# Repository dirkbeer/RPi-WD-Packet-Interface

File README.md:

Note: Schematic and board modified by dirkbeer to use an RJ-45 instead of a DB-9 connector. The RJ-45 pinout used is for the microphone connector on Baofeng mobile radios (e.g. UV-50x2). The text below is jaymzx's original readme.

# RPi-WD-Packet-Interface - A digital mode soundcard interface for the Raspberry Pi!

I set up an APRS igate using a Raspberry Pi device and a TNC-Pi 'hat'. While troubleshooting some other issues, I inadvertantly damaged the TNC-Pi, so I decided to go with a software TNC application. In this case, I chose [Dire Wolf](https://github.com/wb2osz/direwolf) by WB2OSZ. In his documentation, he specified a simple radio PTT interface that included a 'watchdog timer' to prevent a software issue from locking the radio into transmit. Working with WB2OSZ, I expanded the circuit and created a board with the following features:

### Selectable transmit and receive channels
* I noticed between sound card dongles, the mic input could be on the left or the right channel, depending on how much care the manufacturer put into it. A jumper lets you pick the channel that works with your card. I added a transmit channel selector for the same reason, but also so you can use a 'Y' cable with your stereo sound card and use two interfaces to work with two radios without any cable hacking.

### Transmit audio level pot
* The radio is expecting millivolts of input into its MIC input. Modern sound cards can put out more than 2V peak to peak. This is really bad for distortion and over-deviation. Right now, I use about 40% volume on the sound card, and 20% volume on the pot. The audio is DC isolated with a capacitor to prevent phantom voltage (for electret microphones) from either the sound card or the radio from damaging anything.

### Adjustable watchdog delay
* Most people will use this for packet, but some others may use it for things like RTTY, JT-65, QRSS or any other digital mode that has a long duty cycle. I added a big cap and 25-turn trimmer for a delay adjustable between 0 and 110 seconds with the parts specified. One can solder in a fixed resistor or change values for something that doesn't need to be adjusted. [Calculators](http://www.ohmslawcalculator.com/555-monostable-calculator) are out there.

### DCD (received packet) LED
* The newest version of Dire Wolf can trigger a GPIO pin to signal a successfully decoded packet. Just bring this pin 'high' and the yellow DCD LED will light up. Yay. Good for watching activity at-a-glance from across the shack.

### Selectable single-wire handheld PTT or 'Kenwood' dedicated PTT wire method
* Most HTs use a resistor to ground on the microphone input to trigger PTT. Kenwood/Baofeng and some others have to be different and ground the mic shield to trigger. You can set a jumper to select whatever method you need.
	
### Standard Kantronics DB-9 radio interface
* I already had some cables I made and bought for radios when using my KPC3. The TNC-Pi and (I believe) the TinyTrak and OpenTracker devices use the same standard. This makes it easy to buy cables if you don't want to make them, or re-use ones you already have kicking around. FWIW, I hate DB9 connectors and prefer RJ-45 for these purposes, but I wanted to make it 'standard'. Signalink and RigBlaster use a similar (although RB is reversed) RJ-45 standard, but it's not as prolific. In case someone hates DB-9 as much as I do, I called out the signals on the pads to which they can be directly soldered for a cable, header pins, etc.

### Native 3.3v Rpi logic levels
* Using this board as configured works with the 3.3v logic the RPi uses. If you use another controller (like an Arduino) you *can* use 5V logic as the LMC555 CMOS can handle it without a sweat, but you will need to change the resistor values for the LEDs and transistor bias. You can also skip 3.3v altogether if you want to use it with a 5V microcontroller and use a cheap and widely-available LM555N (and the appropriate resistor changes).

### Uses standard 60mm x 60mm 'Sick of Beige' PCB size
* Just like the [xkcd](https://xkcd.com/927/) comic about standards, there is a new PCB size standard for the Maker crowd called [Sick of Beige](http://dangerousprototypes.com/docs/Sick_of_Beige). They have some cool acrylic cases at [Seeed Studios](http://www.seeedstudio.com/depot/Sick-Of-Beige-Basic-Case-v1-60mm-Square-DP6060-p-1329.html), but you can probably find others or fab up your own. The original board was smaller, but in order to fit into the SoB standard size, the minimum size that would fit the DB-9 connector is 60mm. Please note this is *not* a 'hat' for the RPi. It's a separate board. 

### Open Hardware
* I put the time into it, but like most of my projects, once it's done, it's done. I figure others can benefit from my work, so I may as well pass it on. This project is licensed under [Creative Commons Attribution-ShareAlike](https://creativecommons.org/licenses/by-sa/3.0/), so you can edit it, improve it, remix it into another project, make and sell PCBs or kits, etc. You just need to specify a link back to the original source (here) to comply. It's no big deal.
		
### Readily-available parts
* You probably have most of these parts in your bin, but things like the 3.5mm and DB-9 connectors are available at [SparkFun](https://www.sparkfun.com/). I specified genuine Borne trimpots in the PCB footprints but they are commonly used by others. You can find them at [Mouser](http://www.mouser.com/) or many other places.

You can order a [pre-made PCB from OSH Park](https://oshpark.com/shared_projects/dotsia3r) (with the beautiful purple solder mask as shown). They come in multiples of three, so order some for your friends or make a couple for a multi-rig interface. You can also take the Eagle files and have them made elsewhere, or make your own using a toner transfer or photo etch PCB process. Go nuts.

# Known issues
None at this time. 

# Improvements
I'm kicking around the idea of an RJ-45 version of this board, which would be a simple redesign. I also have on the drawing board an isolated version with transformers and opto-isolated PTT control. I welcome discussion around this, and if you can't wait, feel free to fork this project!

## Enjoy the interface, and see you on the air.

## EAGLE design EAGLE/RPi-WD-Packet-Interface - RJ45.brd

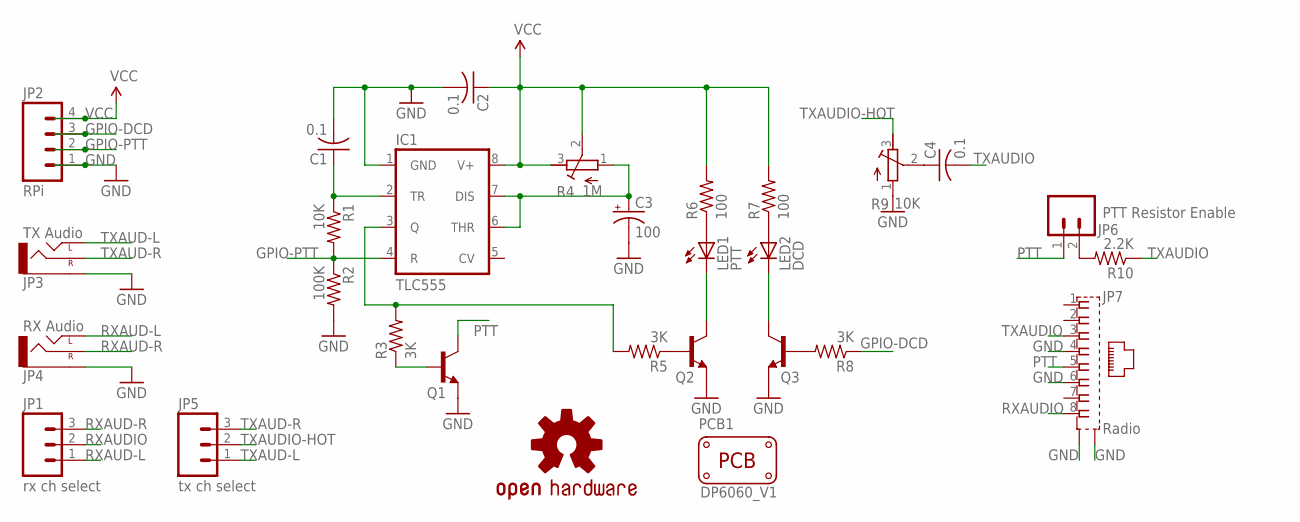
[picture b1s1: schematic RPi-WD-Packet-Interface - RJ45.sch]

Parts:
C1, C2, C4: 0.1; C025-025X050
C3: 100; E2-5
IC1: TLC555; DIL08
JP1: rx ch select; 1X03
JP2: RPi; 1X04
JP3: TX Audio; AUDIO-JACK
JP4: RX Audio; AUDIO-JACK
JP5: tx ch select; 1X03
JP6: PTT Resistor Enable; 1X02
JP7: Radio; 0446200002
LED1: PTT; LED5MM
LED2: DCD; LED5MM
LOGO1: OSHW-LOGOM; OSHW-LOGO-M
PCB1: PCB_DP_SQUARE-6X6; DP6060_V1
Q1: PTT; TO-92-AMMO
Q2: PTT-LED; TO-92-AMMO
Q3: DCD-LED; TO-92-AMMO
R1: 10K; 0207/7
R2: 100K; 0207/7
R3, R5, R8: 3K; 0207/7
R4: 1M; RTRIM3296W
R6, R7: 100; 0207/7
R9: 10K; RTRIM3362P
R10: 2.2K; 0207/7

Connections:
GND: C1.2, C2.2, C3.-, IC1.1 (GND), JP2.1, JP3.SLEEVE, JP4.SLEEVE, JP7.4, JP7.6, JP7.S@1 (S1), JP7.S@2 (S2), Q1.1 (E), Q2.1 (E), Q3.1 (E), R2.2, R9.1
GPIO-DCD: JP2.3, R8.1
GPIO-PTT: IC1.4 (R), JP2.2, R1.2, R2.1
unnamed: LED1.A, R6.1
unnamed: LED2.A, R7.1
unnamed: C1.1, IC1.2 (TR), R1.1
unnamed: C4.1, R9.2
unnamed: C3.+, IC1.6 (THR), IC1.7 (DIS), R4.1 (A)
unnamed: LED1.K (C), Q2.3 (C)
unnamed: Q2.2 (B), R5.1
unnamed: Q1.2 (B), R3.1
unnamed: LED2.K (C), Q3.3 (C)
unnamed: Q3.2 (B), R8.2
unnamed: JP6.2, R10.2
PTT: JP6.1, JP7.5, Q1.3 (C)
PTT_TRIGGER: IC1.3 (Q), R3.2, R5.2
RXAUD-L: JP1.1, JP4.TIP (LEFT)
RXAUD-R: JP1.3, JP4.RING (RIGHT)
RXAUDIO: JP1.2, JP7.8
TXAUD-L: JP3.TIP (LEFT), JP5.1
TXAUD-R: JP3.RING (RIGHT), JP5.3
TXAUDIO: C4.2, JP7.3, R10.1
TXAUDIO-HOT: JP5.2, R9.3
VCC: C2.1, IC1.8 (V+), JP2.4, R4.2 (S), R4.3 (E), R6.2, R7.2

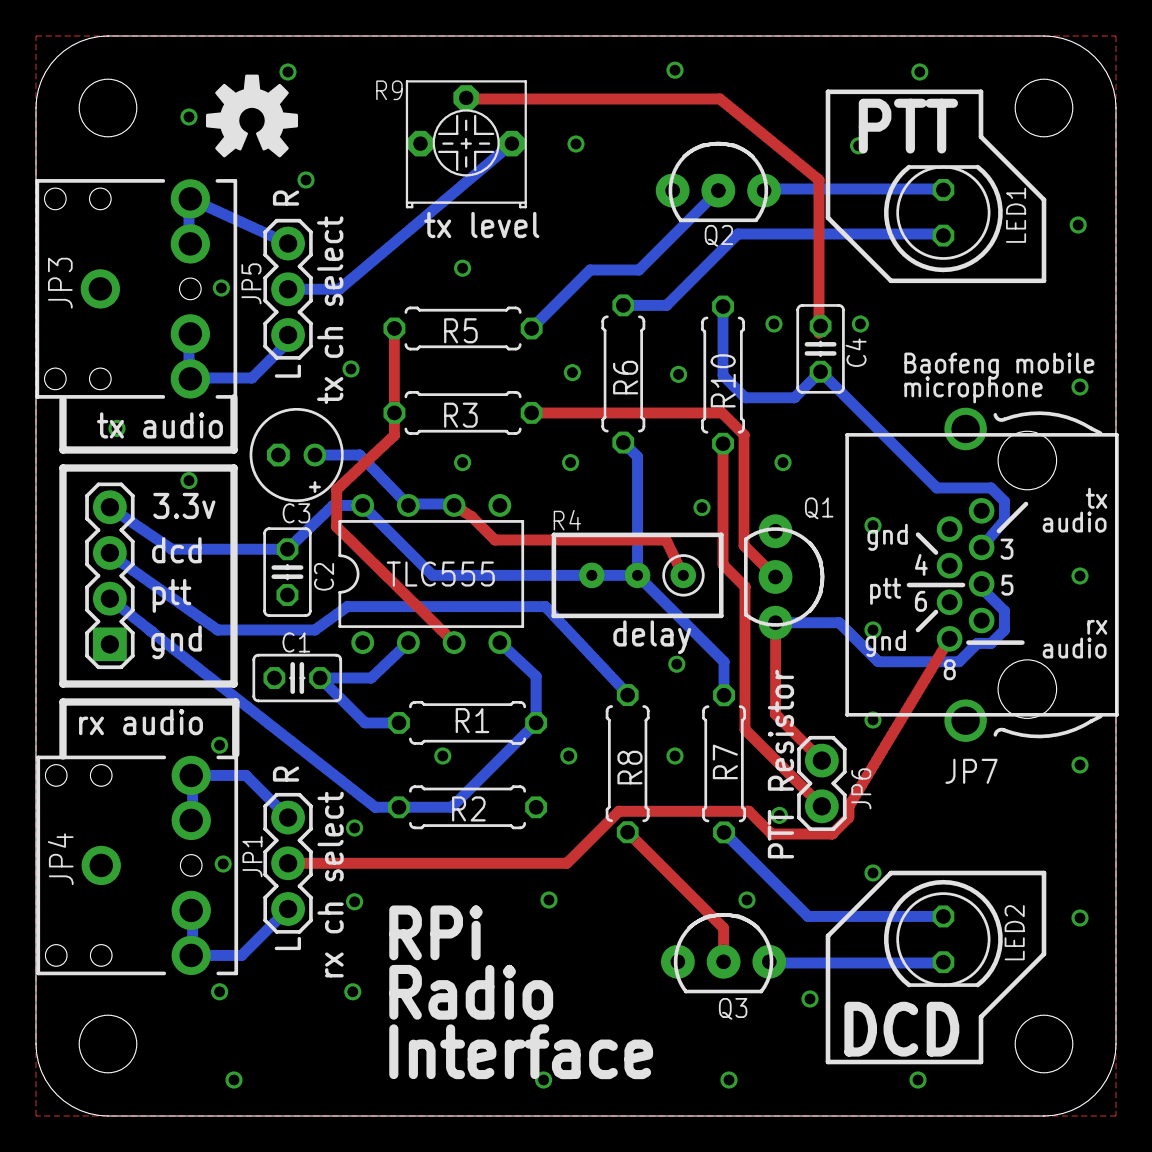
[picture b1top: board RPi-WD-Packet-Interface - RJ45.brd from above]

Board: 2 copper layers, 60.0 x 60.0 mm, 29 parts (0 on the bottom side), 24 nets.

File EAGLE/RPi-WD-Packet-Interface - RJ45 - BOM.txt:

Partlist exported from /home/familybeer/RPi-WD-Packet-Interface/EAGLE/RPi-WD-Packet-Interface - RJ45.sch at 8/26/18 9:48 PM

Part  Value               Device                   Package      Description                                                     MF    MPN        OC_FARNELL PCB_SIZE 
C1    0.1                 C-US025-025X050          C025-025X050 CAPACITOR, American symbol                                                                           
C2    0.1                 C-US025-025X050          C025-025X050 CAPACITOR, American symbol                                                                           
C3    100                 CPOL-USE2-5              E2-5         POLARIZED CAPACITOR, American symbol                                                                 
C4    0.1                 C-US025-025X050          C025-025X050 CAPACITOR, American symbol                                                                           
IC1   TLC555              LM555N                   DIL08        TIMER                                                                                                
JP1   rx ch select        M03PTH                   1X03         Header 3                                                                                             
JP2   RPi                 M04PTH                   1X04         Header 4                                                                                             
JP3   TX Audio            AUDIO-JACKPTH            AUDIO-JACK   3.5mm Audio Jack                                                                                     
JP4   RX Audio            AUDIO-JACKPTH            AUDIO-JACK   3.5mm Audio Jack                                                                                     
JP5   tx ch select        M03PTH                   1X03         Header 3                                                                                             
JP6   PTT Resistor Enable M02PTH                   1X02         Standard 2-pin 0.1" header. Use with                                                                 
JP7   Radio               0446200002               0446200002   RJ-45 INVERTED MODULAR JACK ASSEMBLY WITH RJ-11 KEEPOUT FEATURE MOLEX 0446200002 9251910             
LED1  PTT                 LED5MM                   LED5MM       LED                                                                                                  
LED2  DCD                 LED5MM                   LED5MM       LED                                                                                                  
LOGO1 OSHW-LOGOM          OSHW-LOGOM               OSHW-LOGO-M  Open Source Hardware Logo                                                                            
PCB1  PCB_DP_SQUARE-6X6   PCB_DP_SQUARE-6X6        DP6060_V1    Dangerous Prototypes Standard Square PCB sizes                                              DP6060_V1
Q1    PTT                 TRANSISTOR_NPNTO-92-AMMO TO-92-AMMO   Generic NPN BJT                                                                                      
Q2    PTT-LED             TRANSISTOR_NPNTO-92-AMMO TO-92-AMMO   Generic NPN BJT                                                                                      
Q3    DCD-LED             TRANSISTOR_NPNTO-92-AMMO TO-92-AMMO   Generic NPN BJT                                                                                      
R1    10K                 R-US_0207/7              0207/7       RESISTOR, American symbol                                                                            
R2    100K                R-US_0207/7              0207/7       RESISTOR, American symbol                                                                            
R3    3K                  R-US_0207/7              0207/7       RESISTOR, American symbol                                                                            
R4    1M                  R-TRIMM3296W             RTRIM3296W   Trimm resistor                                                                                       
R5    3K                  R-US_0207/7              0207/7       RESISTOR, American symbol                                                                            
R6    100                 R-US_0207/7              0207/7       RESISTOR, American symbol                                                                            
R7    100                 R-US_0207/7              0207/7       RESISTOR, American symbol                                                                            
R8    3K                  R-US_0207/7              0207/7       RESISTOR, American symbol                                                                            
R9    10K                 RTRIM-3362P              RTRIM3362P   BOURNS 3362 - 1/4" Square Trimpot® Trimming Potentiometer                                            
R10   2.2K                R-US_0207/7              0207/7       RESISTOR, American symbol

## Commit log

2015-08-06 Create gh-pages branch via GitHub
2018-08-27 Replace DB-9 files with RJ-45 version 1.0
2018-08-27 Added RJ-45 Gerber files and made note in Readme
2018-08-27 Added RJ-45 Gerber files, second try
2018-08-27 Removing old BOM and trying to get README to update
2018-08-31 RJ-45 rotation fix & silkscreen update
2018-08-31 Updated renderings and board layout image.
2018-09-24 Update RPi-WD-Packet-Interface - RJ45 - BOM.txt
    specify CMOS 555

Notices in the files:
parts and their libraries:
SparkFun-Connectors: Licensing: Creative Commons ShareAlike 4.0 International - https://creativecommons.org/licenses/by-sa/4.0
